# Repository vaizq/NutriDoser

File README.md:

# NutriDoser - Modular nutrient and pH controller for hydroponics

**NutriDoser** is and open-source prototype of an modular and extensible hydroponics reservoir controller.
Most devices on the market have limited capabilites on the number of nutrients that can be scheduled, but there's no limit with NutriDoser.
**DoserModules** can be daisy chained and controller detects how many of these modules there are and a scheduler takes care that no more than **n** parallel dosers are running.

> ⚠️ **Disclaimer:** This project is still at prototyping stage and should not be used without supervising.

---

## ✨ Key Features

- **Connect unlimited number of dosing pumps**
- **Web interface**
- **Custom PCB that's designed to use mostly basic parts from JLCPCB**
- **Automatic CAN termination**

---

## 🌐 Demo video
https://youtu.be/jbT3SvvVrZw

---

## ⚙️ Stack

- **C++** – Embedded code
- **Javascript + React** – Web interface
- **KiCad** – Hardware design
- **ESP32**
- **STM32**

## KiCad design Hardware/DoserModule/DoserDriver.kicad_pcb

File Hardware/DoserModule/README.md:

# Kicad project for DoserDriver

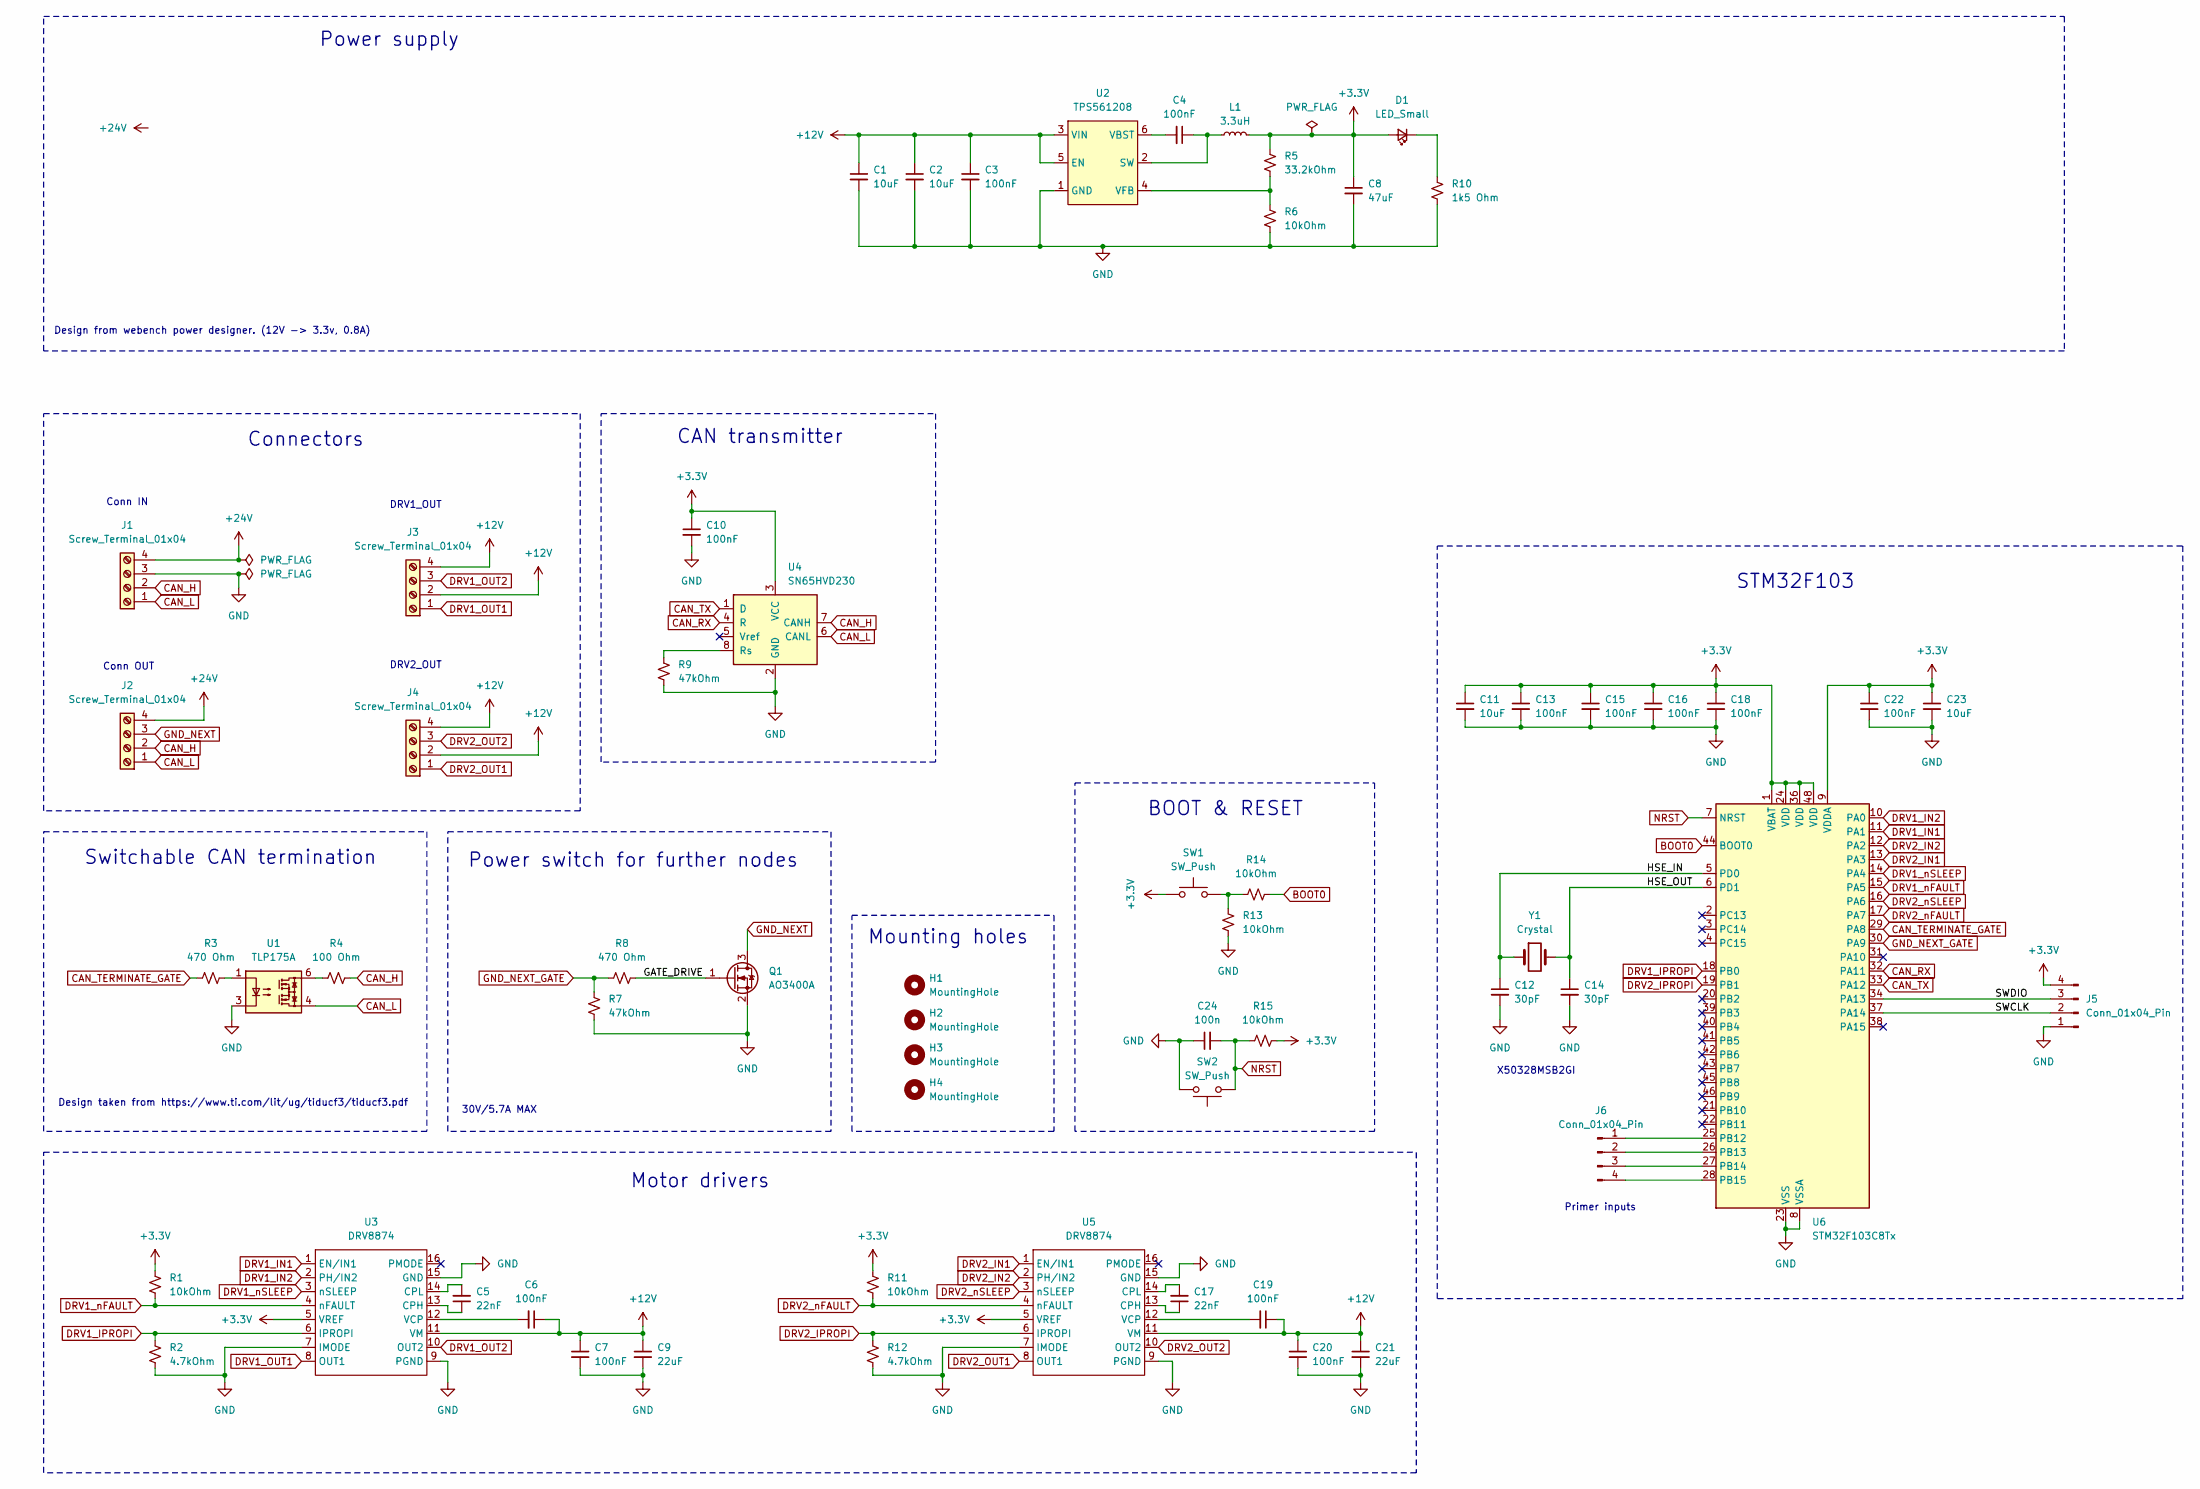
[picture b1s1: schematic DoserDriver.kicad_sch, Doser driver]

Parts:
C1, C2: 10uF; C_0603_1608Metric
C3, C4, C6, C7, C19, C20: 100nF; C_0603_1608Metric
C5, C17: 22nF; C_0402_1005Metric
C8: 47uF; C_0805_2012Metric
C9, C21: 22uF; C_0805_2012Metric
C10, C13, C15, C16, C18, C22: 100nF; C_0402_1005Metric
C11, C23: 10uF; C_0402_1005Metric
C12, C14: 30pF; C_0402_1005Metric
C24: 100n; C_0402_1005Metric
D1: LED_Small; LED_0603_1608Metric
H1, H2, H3, H4: MountingHole; MountingHole_2.2mm_M2
J1, J2, J3, J4: Screw_Terminal_01x04; TerminalBlock_Xinya_XY308-2.54-4P_1x04_P2.54mm_Horizontal
J5, J6: Conn_01x04_Pin; PinHeader_1x04_P2.54mm_Vertical
L1: 3.3uH; L_Sunlord_MWSA0402S
Q1: AO3400A; SOT-23
R1, R6, R11, R13, R14, R15: 10kOhm; R_0402_1005Metric
R2, R12: 4.7kOhm; R_0402_1005Metric
R3, R8: 470 Ohm; R_0402_1005Metric
R4: 100 Ohm; R_1206_3216Metric
R5: 33.2kOhm; R_0402_1005Metric
R7, R9: 47kOhm; R_0402_1005Metric
R10: 1k5 Ohm; R_0402_1005Metric
SW1, SW2: SW_Push; SW_Push_1P1T_XKB_TS-1187A
U1: TLP175A; MFSOP6-4_4.4x3.6mm_P1.27mm
U2: TPS561208; SOT-23-6
U3, U5: DRV8874; HTSSOP-16-1EP_4.4x5mm_P0.65mm_EP3.4x5mm_Mask2.46x2.31mm
U4: SN65HVD230; SOIC-8_3.9x4.9mm_P1.27mm
U6: STM32F103C8Tx; LQFP-48_7x7mm_P0.5mm
Y1: Crystal; Crystal_SMD_5032-2Pin_5.0x3.2mm

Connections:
+3.3V: C8.1, C10.1, C11.1, C13.1, C15.1, C16.1, C18.1, C22.1, C23.1, D1.2 (A), J5.4, L1.2, R1.1, R5.1, R11.1, R15.2, SW1.1, U3.5 (VREF), U4.3 (VCC), U5.5 (VREF), U6.1 (VBAT), U6.9 (VDDA), U6.24 (VDD), U6.36 (VDD), U6.48 (VDD)
/GATE_DRIVE: Q1.1 (G), R8.2
/HSE_IN: C12.1, U6.5 (PD0), Y1.1
/HSE_OUT: C14.1, U6.6 (PD1), Y1.2
/SWCLK: J5.2, U6.37 (PA14)
/SWDIO: J5.3, U6.34 (PA13)
BOOT0: R14.2, U6.44 (BOOT0)
CAN_H: J1.2, J2.2, R4.2, U4.7 (CANH)
CAN_L: J1.1, J2.1, U1.4, U4.6 (CANL)
CAN_RX: U4.4 (R), U6.32 (PA11)
CAN_TERMINATE_GATE: R3.2, U6.29 (PA8)
CAN_TX: U4.1 (D), U6.33 (PA12)
DRV1_IN1: U3.1 (EN/IN1), U6.11 (PA1)
DRV1_IN2: U3.2 (PH/IN2), U6.10 (PA0)
DRV1_IPROPI: R2.1, U3.6 (IPROPI), U6.18 (PB0)
DRV1_OUT1: J3.1, U3.8 (OUT1)
DRV1_OUT2: J3.3, U3.10 (OUT2)
DRV1_nFAULT: R1.2, U3.4 (nFAULT), U6.15 (PA5)
DRV1_nSLEEP: U3.3 (nSLEEP), U6.14 (PA4)
DRV2_IN1: U5.1 (EN/IN1), U6.13 (PA3)
DRV2_IN2: U5.2 (PH/IN2), U6.12 (PA2)
DRV2_IPROPI: R12.1, U5.6 (IPROPI), U6.19 (PB1)
DRV2_OUT1: J4.1, U5.8 (OUT1)
DRV2_OUT2: J4.3, U5.10 (OUT2)
DRV2_nFAULT: R11.2, U5.4 (nFAULT), U6.17 (PA7)
DRV2_nSLEEP: U5.3 (nSLEEP), U6.16 (PA6)
GND: C1.2, C2.2, C3.2, C7.2, C8.2, C9.2, C10.2, C11.2, C12.2, C13.2, C14.2, C15.2, C16.2, C18.2, C20.2, C21.2, C22.2, C23.2, C24.1, J1.3, J5.1, Q1.2 (S), R2.2, R6.2, R7.2, R9.1, R10.1, R12.2, R13.2, SW2.2, U1.3, U2.1 (GND), U3.7 (IMODE), U3.9 (PGND), U3.15 (GND), U4.2 (GND), U5.7 (IMODE), U5.9 (PGND), U5.15 (GND), U6.8 (VSSA), U6.23 (VSS), U6.35 (VSS), U6.47 (VSS)
GND_NEXT: J2.3, Q1.3 (D)
GND_NEXT_GATE: R7.1, R8.1, U6.30 (PA9)
NRST: C24.2, R15.1, SW2.1, U6.7 (NRST)
unnamed: D1.1 (K), R10.2
unnamed: J6.1, U6.25 (PB12)
unnamed: J6.2, U6.26 (PB13)
unnamed: J6.3, U6.27 (PB14)
unnamed: J6.4, U6.28 (PB15)
unnamed: R3.1, U1.1
unnamed: R4.1, U1.6
unnamed: R13.1, R14.1, SW1.2
unnamed: C4.1, L1.1, U2.2 (SW)
unnamed: C4.2, U2.6 (VBST)
unnamed: R5.2, R6.1, U2.4 (VFB)
unnamed: C5.1, U3.13 (CPH)
unnamed: C5.2, U3.14 (CPL)
unnamed: C6.2, U3.12 (VCP)
unnamed: R9.2, U4.8 (Rs)
unnamed: C17.1, U5.13 (CPH)
unnamed: C17.2, U5.14 (CPL)
unnamed: C19.2, U5.12 (VCP)

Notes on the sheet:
Conn OUT
Motor drivers
Mounting holes
X50328MSB2GI
Design from webench power designer. (12V -> 3.3v, 0.8A)
BOOT & RESET
30V/5.7A MAX
Connectors
Primer inputs
STM32F103
Conn IN
Switchable CAN termination
Design taken from https://www.ti.com/lit/ug/tiducf3/tiducf3.pdf
CAN transmitter
Power switch for further nodes
DRV1_OUT
Power supply
DRV2_OUT

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
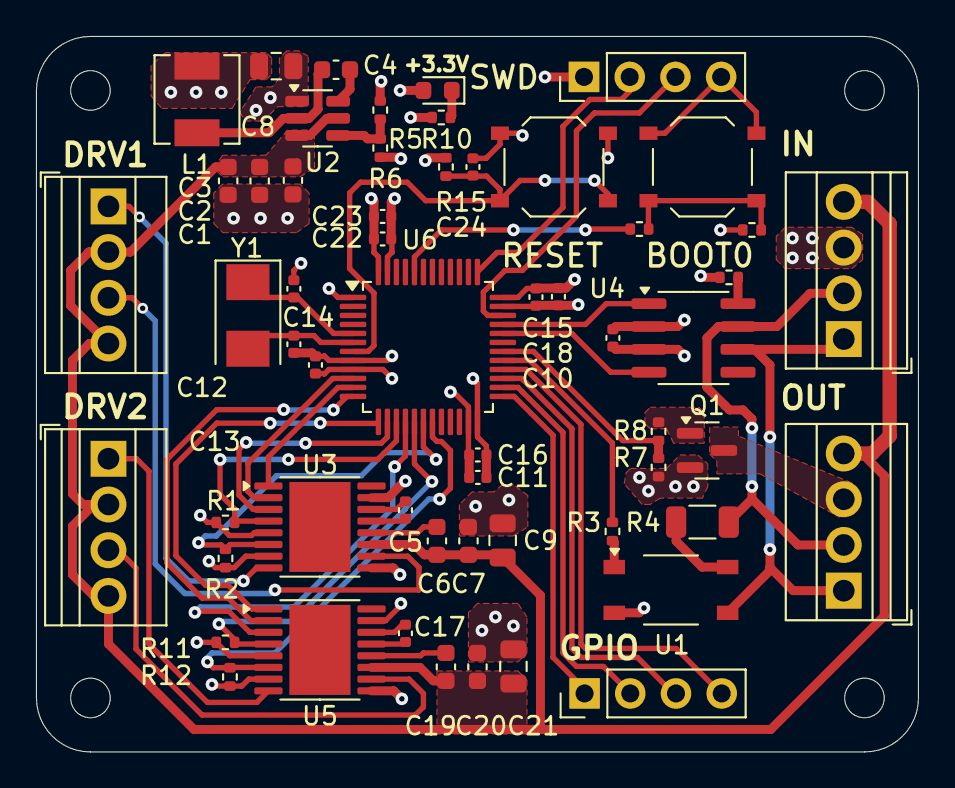
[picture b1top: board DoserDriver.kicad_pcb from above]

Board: 4 copper layers, 49.0 x 39.8 mm, 61 parts (0 on the bottom side), 49 nets.

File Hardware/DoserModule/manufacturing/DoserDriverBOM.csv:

Comment,Designator,Footprint,LCSC
"10uF","C1,C2","Capacitor_SMD:C_0603_1608Metric","C96446"
"100nF","C10,C13,C15,C16,C18,C22,C24","Capacitor_SMD:C_0402_1005Metric","C1525"
"10uF","C11,C23","Capacitor_SMD:C_0402_1005Metric","C15525"
"30pF","C12,C14","Capacitor_SMD:C_0402_1005Metric","C1570"
"100nF","C3,C4,C6,C7,C19,C20","Capacitor_SMD:C_0603_1608Metric","C14663"
"22nF","C5,C17","Capacitor_SMD:C_0402_1005Metric","C1532"
"47uF","C8","Capacitor_SMD:C_0805_2012Metric","C16780"
"22uF","C9,C21","Capacitor_SMD:C_0805_2012Metric","C45783"
"LED_Small","D1","LED_SMD:LED_0603_1608Metric","C2286"
"3.3uH","L1","Inductor_SMD:L_Sunlord_MWSA0402S","C408336"
"AO3400A","Q1","Package_TO_SOT_SMD:SOT-23","C20917"
"10kOhm","R1,R6,R11,R13,R14,R15","Resistor_SMD:R_0402_1005Metric","C25744"
"1k5 Ohm","R10","Resistor_SMD:R_0402_1005Metric","C25867"
"4.7kOhm","R2,R12","Resistor_SMD:R_0402_1005Metric","C25900"
"470 Ohm","R3,R8","Resistor_SMD:R_0402_1005Metric","C25117"
"100 Ohm","R4","Resistor_SMD:R_1206_3216Metric","C17901"
"33.2kOhm","R5","Resistor_SMD:R_0402_1005Metric","C122548"
"47kOhm","R7,R9","Resistor_SMD:R_0402_1005Metric","C25792"
"SW_Push","SW1,SW2","AutoDoser:SW_Push_1P1T_XKB_TS-1187A","C318884"
"TLP175A","U1","Package_SO:MFSOP6-4_4.4x3.6mm_P1.27mm","C141522"
"TPS561208","U2","Package_TO_SOT_SMD:SOT-23-6","C138335"
"DRV8874","U3,U5","AutoDoser:HTSSOP-16-1EP_4.4x5mm_P0.65mm_EP3.4x5mm_Mask2.46x2.31mm","C1855818"
"SN65HVD230","U4","Package_SO:SOIC-8_3.9x4.9mm_P1.27mm","C12084"
"STM32F103C8Tx","U6","Package_QFP:LQFP-48_7x7mm_P0.5mm","C8734"
"Crystal","Y1","Crystal:Crystal_SMD_5032-2Pin_5.0x3.2mm","C115962"

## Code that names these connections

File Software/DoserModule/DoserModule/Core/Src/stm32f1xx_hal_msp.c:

/* USER CODE BEGIN Header */
/**
  ******************************************************************************
  * @file         stm32f1xx_hal_msp.c
  * @brief        This file provides code for the MSP Initialization
  *               and de-Initialization codes.
  ******************************************************************************
  * @attention
  *
  * Copyright (c) 2024 STMicroelectronics.
  * All rights reserved.
  *
  * This software is licensed under terms that can be found in the LICENSE file
  * in the root directory of this software component.
  * If no LICENSE file comes with this software, it is provided AS-IS.
  *
  ******************************************************************************
  */
/* USER CODE END Header */

/* Includes ------------------------------------------------------------------*/
#include "main.h"
/* USER CODE BEGIN Includes */

/* USER CODE END Includes */

/* Private typedef -----------------------------------------------------------*/
/* USER CODE BEGIN TD */

/* USER CODE END TD */

/* Private define ------------------------------------------------------------*/
/* USER CODE BEGIN Define */

/* USER CODE END Define */

/* Private macro -------------------------------------------------------------*/
/* USER CODE BEGIN Macro */

/* USER CODE END Macro */

/* Private variables ---------------------------------------------------------*/
/* USER CODE BEGIN PV */

/* USER CODE END PV */

/* Private function prototypes -----------------------------------------------*/
/* USER CODE BEGIN PFP */

/* USER CODE END PFP */

/* External functions --------------------------------------------------------*/
/* USER CODE BEGIN ExternalFunctions */

/* USER CODE END ExternalFunctions */

/* USER CODE BEGIN 0 */

/* USER CODE END 0 */

void HAL_TIM_MspPostInit(TIM_HandleTypeDef *htim);
                    /**
  * Initializes the Global MSP.
  */
void HAL_MspInit(void)
{

  /* USER CODE BEGIN MspInit 0 */

  /* USER CODE END MspInit 0 */

  __HAL_RCC_AFIO_CLK_ENABLE();
  __HAL_RCC_PWR_CLK_ENABLE();

  /* System interrupt init*/

  /** NOJTAG: JTAG-DP Disabled and SW-DP Enabled
  */
  __HAL_AFIO_REMAP_SWJ_NOJTAG();

  /* USER CODE BEGIN MspInit 1 */

  /* USER CODE END MspInit 1 */
}

/**
* @brief ADC MSP Initialization
* This function configures the hardware resources used in this example
* @param hadc: ADC handle pointer
* @retval None
*/
void HAL_ADC_MspInit(ADC_HandleTypeDef* hadc)
{
  GPIO_InitTypeDef GPIO_InitStruct = {0};
  if(hadc->Instance==ADC1)
  {
  /* USER CODE BEGIN ADC1_MspInit 0 */

  /* USER CODE END ADC1_MspInit 0 */
    /* Peripheral clock enable */
    __HAL_RCC_ADC1_CLK_ENABLE();

    __HAL_RCC_GPIOB_CLK_ENABLE();
    /**ADC1 GPIO Configuration
    PB0     ------> ADC1_IN8
    PB1     ------> ADC1_IN9
    */
    GPIO_InitStruct.Pin = GPIO_PIN_0|GPIO_PIN_1;
    GPIO_InitStruct.Mode = GPIO_MODE_ANALOG;
    HAL_GPIO_Init(GPIOB, &GPIO_InitStruct);

  /* USER CODE BEGIN ADC1_MspInit 1 */

  /* USER CODE END ADC1_MspInit 1 */
  }

}

/**
* @brief ADC MSP De-Initialization
* This function freeze the hardware resources used in this example
* @param hadc: ADC handle pointer
* @retval None
*/
void HAL_ADC_MspDeInit(ADC_HandleTypeDef* hadc)
{
  if(hadc->Instance==ADC1)
  {
  /* USER CODE BEGIN ADC1_MspDeInit 0 */

  /* USER CODE END ADC1_MspDeInit 0 */
    /* Peripheral clock disable */
    __HAL_RCC_ADC1_CLK_DISABLE();

    /**ADC1 GPIO Configuration
    PB0     ------> ADC1_IN8
    PB1     ------> ADC1_IN9
    */
    HAL_GPIO_DeInit(GPIOB, GPIO_PIN_0|GPIO_PIN_1);

  /* USER CODE BEGIN ADC1_MspDeInit 1 */

  /* USER CODE END ADC1_MspDeInit 1 */
  }

}

/**
* @brief CAN MSP Initialization
* This function configures the hardware resources used in this example
* @param hcan: CAN handle pointer
* @retval None
*/
void HAL_CAN_MspInit(CAN_HandleTypeDef* hcan)
{
  GPIO_InitTypeDef GPIO_InitStruct = {0};
  if(hcan->Instance==CAN1)
  {
  /* USER CODE BEGIN CAN1_MspInit 0 */

  /* USER CODE END CAN1_MspInit 0 */
    /* Peripheral clock enable */
    __HAL_RCC_CAN1_CLK_ENABLE();

    __HAL_RCC_GPIOA_CLK_ENABLE();
    /**CAN GPIO Configuration
    PA11     ------> CAN_RX
    PA12     ------> CAN_TX
    */
    GPIO_InitStruct.Pin = GPIO_PIN_11;
    GPIO_InitStruct.Mode = GPIO_MODE_INPUT;
    GPIO_InitStruct.Pull = GPIO_NOPULL;
    HAL_GPIO_Init(GPIOA, &GPIO_InitStruct);

    GPIO_InitStruct.Pin = GPIO_PIN_12;
    GPIO_InitStruct.Mode = GPIO_MODE_AF_PP;
    GPIO_InitStruct.Speed = GPIO_SPEED_FREQ_HIGH;
    HAL_GPIO_Init(GPIOA, &GPIO_InitStruct);

  /* USER CODE BEGIN CAN1_MspInit 1 */

  /* USER CODE END CAN1_MspInit 1 */
  }

}

/**
* @brief CAN MSP De-Initialization
* This function freeze the hardware resources used in this example
* @param hcan: CAN handle pointer
* @retval None
*/
void HAL_CAN_MspDeInit(CAN_HandleTypeDef* hcan)
{
  if(hcan->Instance==CAN1)
  {
  /* USER CODE BEGIN CAN1_MspDeInit 0 */

  /* USER CODE END CAN1_MspDeInit 0 */
    /* Peripheral clock disable */
    __HAL_RCC_CAN1_CLK_DISABLE();

    /**CAN GPIO Configuration
    PA11     ------> CAN_RX
    PA12     ------> CAN_TX
    */
    HAL_GPIO_DeInit(GPIOA, GPIO_PIN_11|GPIO_PIN_12);

  /* USER CODE BEGIN CAN1_MspDeInit 1 */

  /* USER CODE END CAN1_MspDeInit 1 */
  }

}

/**
* @brief TIM_Base MSP Initialization
* This function configures the hardware resources used in this example
* @param htim_base: TIM_Base handle pointer
* @retval None
*/
void HAL_TIM_Base_MspInit(TIM_HandleTypeDef* htim_base)
{
  if(htim_base->Instance==TIM1)
  {
  /* USER CODE BEGIN TIM1_MspInit 0 */

  /* USER CODE END TIM1_MspInit 0 */
    /* Peripheral clock enable */
    __HAL_RCC_TIM1_CLK_ENABLE();
    /* TIM1 interrupt Init */
    HAL_NVIC_SetPriority(TIM1_UP_IRQn, 0, 0);
    HAL_NVIC_EnableIRQ(TIM1_UP_IRQn);
  /* USER CODE BEGIN TIM1_MspInit 1 */

  /* USER CODE END TIM1_MspInit 1 */
  }
  else if(htim_base->Instance==TIM2)
  {
  /* USER CODE BEGIN TIM2_MspInit 0 */

  /* USER CODE END TIM2_MspInit 0 */
    /* Peripheral clock enable */
    __HAL_RCC_TIM2_CLK_ENABLE();
  /* USER CODE BEGIN TIM2_MspInit 1 */

  /* USER CODE END TIM2_MspInit 1 */
  }

}

void HAL_TIM_MspPostInit(TIM_HandleTypeDef* htim)
{
  GPIO_InitTypeDef GPIO_InitStruct = {0};
  if(htim->Instance==TIM2)
  {
  /* USER CODE BEGIN TIM2_MspPostInit 0 */

  /* USER CODE END TIM2_MspPostInit 0 */

    __HAL_RCC_GPIOA_CLK_ENABLE();
    /**TIM2 GPIO Configuration
    PA0-WKUP     ------> TIM2_CH1
    PA1     ------> TIM2_CH2
    PA2     ------> TIM2_CH3
    PA3     ------> TIM2_CH4
    */
    GPIO_InitStruct.Pin = GPIO_PIN_0|GPIO_PIN_1|GPIO_PIN_2|GPIO_PIN_3;
    GPIO_InitStruct.Mode = GPIO_MODE_AF_PP;
    GPIO_InitStruct.Speed = GPIO_SPEED_FREQ_LOW;
    HAL_GPIO_Init(GPIOA, &GPIO_InitStruct);

  /* USER CODE BEGIN TIM2_MspPostInit 1 */

  /* USER CODE END TIM2_MspPostInit 1 */
  }

}
/**
* @brief TIM_Base MSP De-Initialization
* This function freeze the hardware resources used in this example
* @param htim_base: TIM_Base handle pointer
* @retval None
*/
void HAL_TIM_Base_MspDeInit(TIM_HandleTypeDef* htim_base)
{
  if(htim_base->Instance==TIM1)
  {
  /* USER CODE BEGIN TIM1_MspDeInit 0 */

  /* USER CODE END TIM1_MspDeInit 0 */
    /* Peripheral clock disable */
    __HAL_RCC_TIM1_CLK_DISABLE();

    /* TIM1 interrupt DeInit */
    HAL_NVIC_DisableIRQ(TIM1_UP_IRQn);
  /* USER CODE BEGIN TIM1_MspDeInit 1 */

  /* USER CODE END TIM1_MspDeInit 1 */
  }
  else if(htim_base->Instance==TIM2)
  {
  /* USER CODE BEGIN TIM2_MspDeInit 0 */

  /* USER CODE END TIM2_MspDeInit 0 */
    /* Peripheral clock disable */
    __HAL_RCC_TIM2_CLK_DISABLE();
  /* USER CODE BEGIN TIM2_MspDeInit 1 */

  /* USER CODE END TIM2_MspDeInit 1 */
  }

}

/* USER CODE BEGIN 1 */

/* USER CODE END 1 */

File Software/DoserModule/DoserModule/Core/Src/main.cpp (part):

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  /*Configure GPIO pin Output Level */
  HAL_GPIO_WritePin(GPIOB, GPIO_PIN_12|GPIO_PIN_13|GPIO_PIN_14|GPIO_PIN_15, GPIO_PIN_RESET);

  /*Configure GPIO pins : PA4 PA6 PA8 PA9 */
  GPIO_InitStruct.Pin = GPIO_PIN_4|GPIO_PIN_6|GPIO_PIN_8|GPIO_PIN_9;
  GPIO_InitStruct.Mode = GPIO_MODE_OUTPUT_PP;
  GPIO_InitStruct.Pull = GPIO_NOPULL;
  GPIO_InitStruct.Speed = GPIO_SPEED_FREQ_LOW;
  HAL_GPIO_Init(GPIOA, &GPIO_InitStruct);

  /*Configure GPIO pins : PA5 PA7 */
  GPIO_InitStruct.Pin = GPIO_PIN_5|GPIO_PIN_7;
  GPIO_InitStruct.Mode = GPIO_MODE_INPUT;
  GPIO_InitStruct.Pull = GPIO_NOPULL;
  HAL_GPIO_Init(GPIOA, &GPIO_InitStruct);

  /*Configure GPIO pins : PB12 PB13 PB14 PB15 */
  GPIO_InitStruct.Pin = GPIO_PIN_12|GPIO_PIN_13|GPIO_PIN_14|GPIO_PIN_15;
  GPIO_InitStruct.Mode = GPIO_MODE_OUTPUT_PP;
  GPIO_InitStruct.Pull = GPIO_NOPULL;
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
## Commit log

2025-04-14 Initial commit for the new repo
2025-04-14 readme
